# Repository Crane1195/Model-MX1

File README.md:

# Model MX1
A single switch PCB with a Kailh hotswap socket, a 2 pin THT LED mount, a mount for both THT and SMT (0805) resistors, and a mount for a 3 position 2.54mm pitch screw terminal.

## License
This project is licenced under the GNU GPL Version 3. [See the included LICENSE file for details](LICENSE).

## Support my work
I set up a donation link for people who appreciate my work and wish to donate. Donations are greatly appreciated, but are far from necessary:

https://www.paypal.com/donate/?hosted_button_id=NFDEML5FKR8N8

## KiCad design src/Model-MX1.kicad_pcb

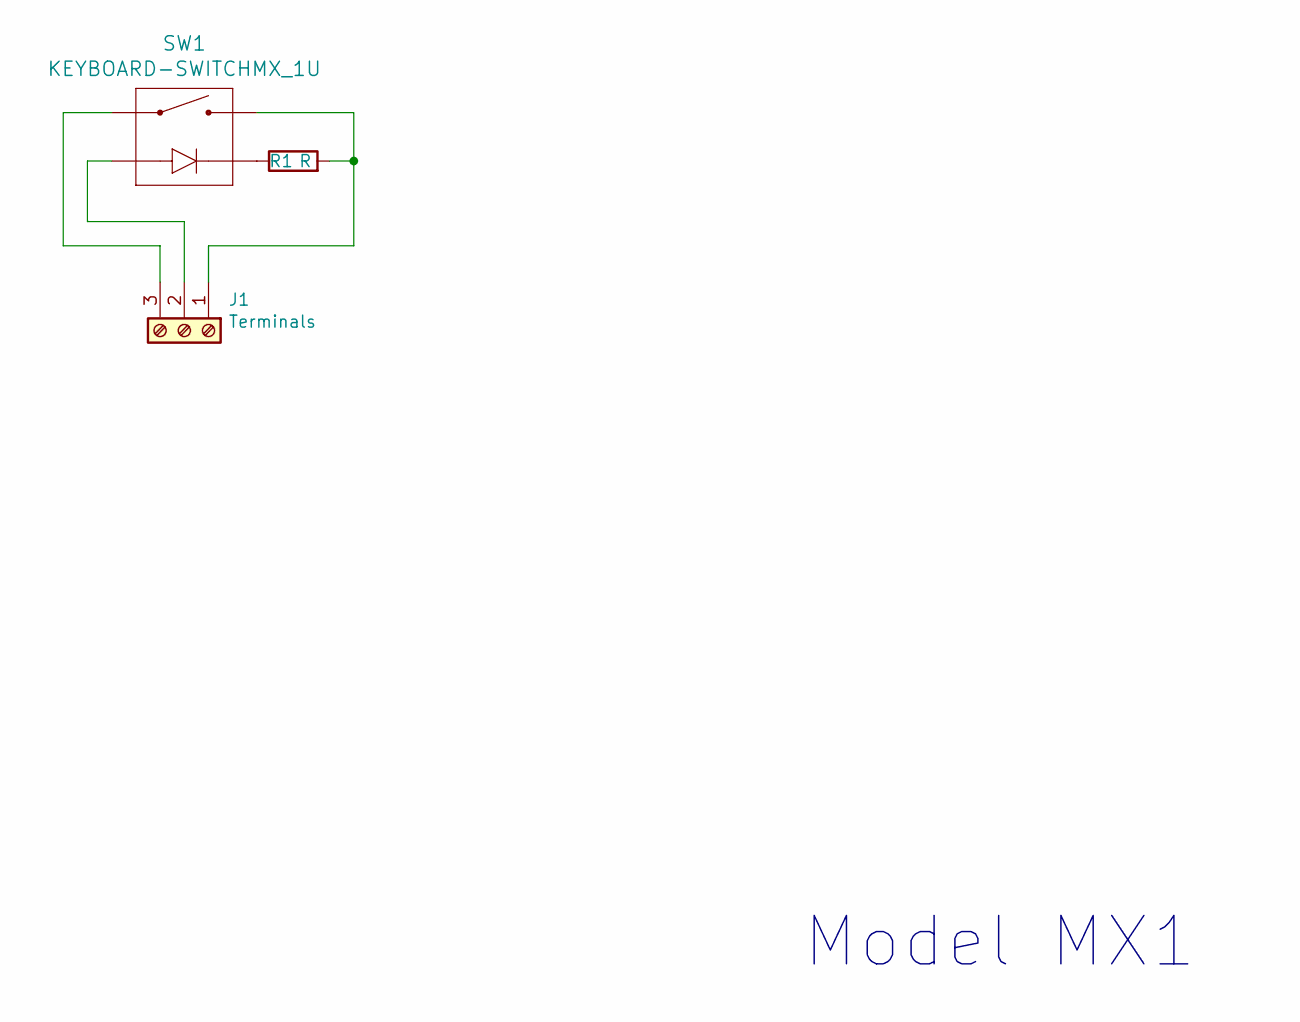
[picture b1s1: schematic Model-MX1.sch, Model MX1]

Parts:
J1: Terminals; TerminalBlock_Phoenix_MPT-0,5-3-2.54_1x03_P2.54mm_Horizontal
R1: R; R_SMD+THT
SW1: KEYBOARD-SWITCHMX_1U; MXOnly-1U-Hotswap-LED

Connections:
unnamed: J1.1, R1.2, SW1.S2
unnamed: J1.2, SW1.A
unnamed: J1.3, SW1.S1
unnamed: R1.1, SW1.C

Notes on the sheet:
Model MX1

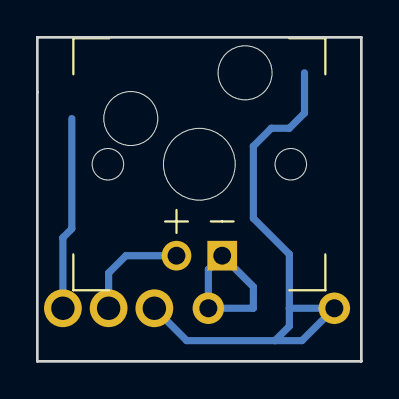
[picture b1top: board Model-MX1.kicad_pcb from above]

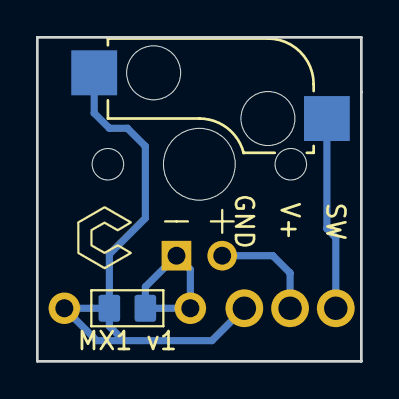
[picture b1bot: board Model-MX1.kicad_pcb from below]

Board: 2 copper layers, 18.0 x 18.0 mm, 3 parts (2 on the bottom side), 4 nets.

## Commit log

2022-03-01 Add PCB files
2022-03-05 Add README info and images.
